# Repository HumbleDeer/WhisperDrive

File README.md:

# WhisperDrive

> A 2-wire fan control board meant to silence the PWM noise.

A project aiming to create a PCB that provides the means to supply your 3D-printer's fans with a smoothed DC voltage using a PWM-controlled input signal.

The main filter circuit can also be used with an existing low-side switched MOSFET port on a 3D-printer motherboard, although there are no PCB files for this purpose at this time.

## Documentation

- [Building the board](docs/build.md)
- [Configuration](docs/config.md)

## Get in touch

You can get in touch with me and other people affiliated with this project through our Discord server for Armchair Heavy Industries.

## License

This source describes Open Hardware and is licensed under the CERN-OHL-S v2 or any later version.  
You may redistribute and modify this source and make products using it under the terms of the CERN-OHL-S v2. (<https://ohwr.org/cern_ohl_s_v2.txt>)

This source is distributed WITHOUT ANY EXPRESS OR IMPLIED WARRANTY, INCLUDING OF MERCHANTABILITY, SATISFACTORY QUALITY AND FITNESS FOR A PARTICULAR PURPOSE. Please see the CERN-OHL-S v2 for applicable conditions.

Source location: <https://github.com/HumbleDeer/WhisperDrive>

As per CERN-OHL-S v2 section 4, should You produce hardware based on this source, You must where practicable maintain the Source Location visible on the PCB.

## Other projects

Some other projects that may be worth checking out. These are probably friends of the communities I hang out in.

- [NyoomiesKME](https://github.com/comradef191/NyoomiesKME)  
  A Pico or BlackPill powered expansion board for Klipper, with support for four motors running in SPI or UART, and ability to run higher currents than most mainboards.
- [Kalico](https://github.com/KalicoCrew/kalico)  
  Formerly known as DangerKlipper
  > This is a community-maintained fork of the Klipper firmware. Our goal is to support features and behavior that could be "risky" if used incorrectly.

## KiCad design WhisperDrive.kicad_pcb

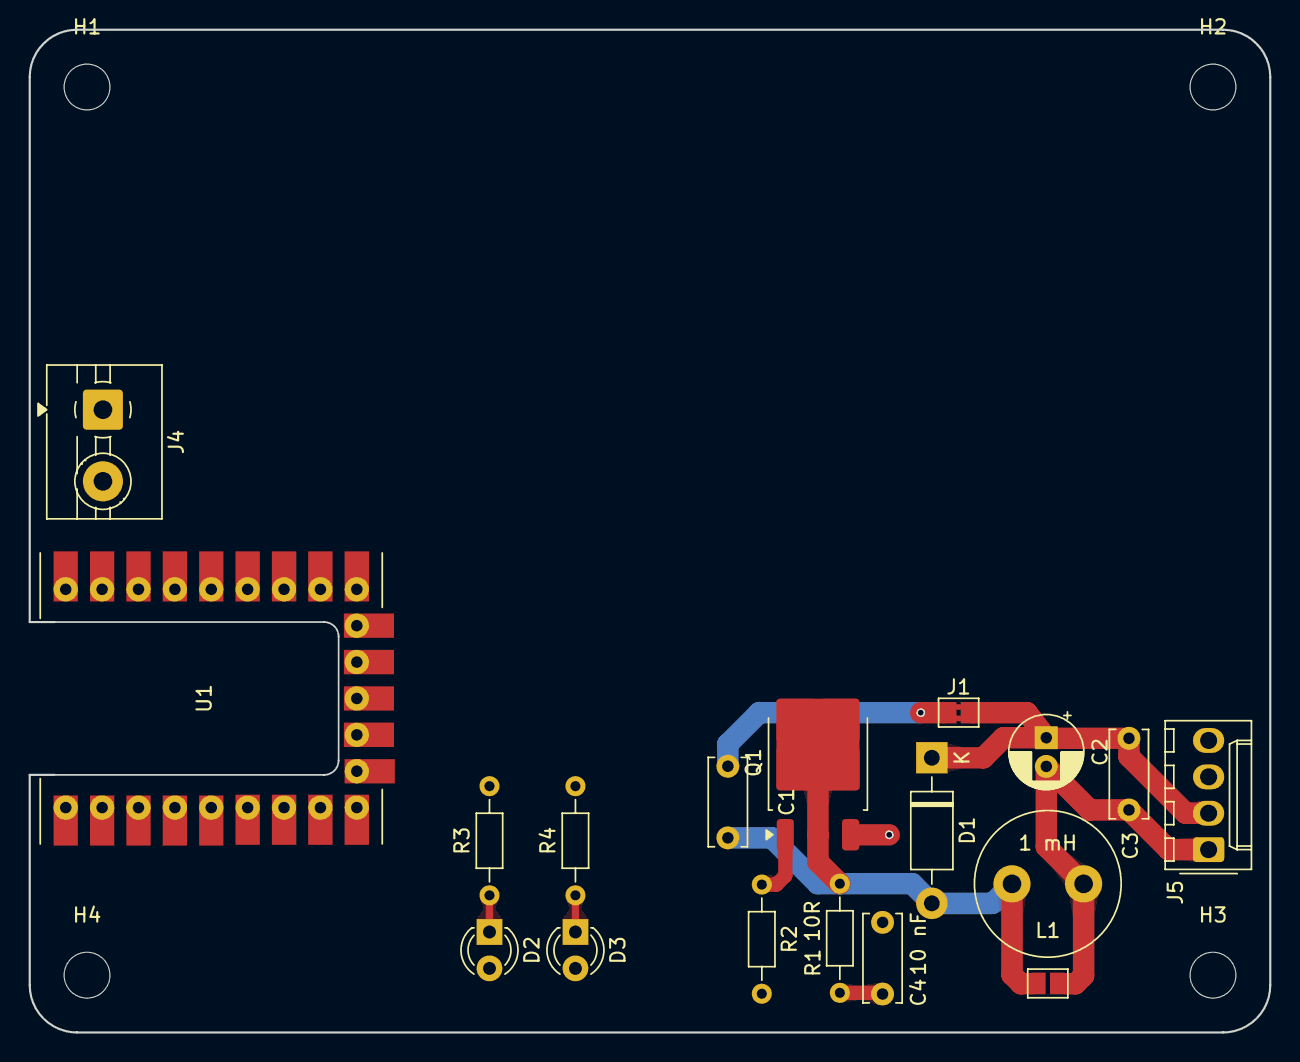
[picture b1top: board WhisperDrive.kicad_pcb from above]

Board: 2 copper layers, 86.6 x 70.0 mm, 22 parts (0 on the bottom side), 10 nets.

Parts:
C1, C3, C4: 10 nF; C_Disc_D6.0mm_W2.5mm_P5.00mm
C2: 10 uF; CP_Radial_D5.0mm_P2.00mm
D1: Schottky; D_DO-41_SOD81_P10.16mm_Horizontal
D2: RED; LED_D3.0mm_Clear
D3: GREEN; LED_D3.0mm_Clear
H1, H2, H3, H4: MountingHole_Pad; MountingHole_3.2mm_M3
J1: VFAN1 Enable; SolderJumper-2_P1.3mm_Bridged2Bar_Pad1.0x1.5mm
J2: FAN1_BYPASS; SolderJumper-2_P1.3mm_Open_Pad1.0x1.5mm
J4: Power In; TerminalBlock_MaiXu_MX126-5.0-02P_1x02_P5.00mm
J5: Fan 1; Molex_KK-254_AE-6410-04A_1x04_P2.54mm_Vertical
L1: 1 mH; L_Radial_D10.0mm_P5.00mm_Fastron_07M
Q1: 25N06; TO-252-3_TabPin2
R1: 10R; R_Axial_DIN0204_L3.6mm_D1.6mm_P7.62mm_Horizontal
R2: 10K; R_Axial_DIN0204_L3.6mm_D1.6mm_P7.62mm_Horizontal
R3, R4: 4K7; R_Axial_DIN0204_L3.6mm_D1.6mm_P7.62mm_Horizontal
U1: RP2040-Zero; RP2040 Zero

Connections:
FAN1_NEG: C2.2, C3.2, J2.1 (A), J5.1, L1.1
FAN1_POS: C2.1, C3.1, D1.1 (K), J1.2 (B), J5.2
GND: C4.2, J4.2, Q1.3 (S), R2.2, R3.2, R4.2, U1.2 (GND)
MOS1_DRV: Q1.1 (G), R2.1
unnamed: C4.1, R1.2
unnamed: C1.2, D1.2 (A), J2.2 (B), L1.2, Q1.2 (D), R1.1
unnamed: D2.1 (K), R3.1
unnamed: D3.1 (K), R4.1
VBUS: D3.2 (A), U1.1 (5V)
VFAN: C1.1, D2.2 (A), J1.1 (A), J4.1

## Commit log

2024-05-30 Initial: Readme and license
2024-05-30 Docs pages in docs folder
2024-05-30 Init KiCad project
2024-05-30 Add ad-hoc model circuit schematic
2024-05-30 Add footprint/symbol library for RP2040-Zero
2024-05-30 Planned / future features list
2025-04-11 Further component selection and preliminary one-block layout for the switching only. Need buffer. Removed second block.
2025-04-11 DangerKlipper is Kalico now. + More changes not committed in the last commit. Oopsie.
2025-04-17 added: gate driver, second circuit, regulator for driver, optional separate power rail for fan/drive modified: changed global labels to net labels, moved power circuitry to subsheet
